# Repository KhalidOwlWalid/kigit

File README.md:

<div align="center">

# kigit

### Visual diffs for KiCad PCBs and schematics, straight from git.

</div>

**kigit** utilizes the use of git logs in order to allow user to perform diffs between their pcb and schematic files. It provides a proper visual feedback which helps in identifying changes made per commit basis. Hence where its name came from, combination of Ki from KiCAD and git itself (kigit!). 

What it can do:

- Compare your PCB between any two commits, visually
- Show what changed on your symbols and their fields
- Show your buses and where they're routed
- Works without git too: just point it at two folders
- Keep notes and PR-style discussions on why the board changed, and see any commit in 3D
- A bill of materials: part numbers, stock and prices from Mouser and Digi-Key, carts, your inventory, and builds you assemble board by board
- Comes with an example project to try it all on: `kigit example`

Have a look at the demos below to get a feel for it.

## Demonstration

Full documentation can be found here: https://khalidowlwalid.github.io/kigit/

### PCB diff
Hover a trace to light up its whole net and see what was added, removed or changed.

### Schematic diff
Every sheet, with nets computed the way KiCad's netlist does: hover a net, part or bus to see what changed.

### 3D Viewer
Kigit uses kicad-cli backend to render the PCB and displays the 2 commit's board side by side for ease of comparison

<p align="center"><i>The GUI: pick two commits, see what changed on the schematic and PCB, with both boards in 3D (made by KiCad) docked below, views linked.</i></p>

<p align="center"><i>Both commits' boards in 3D, side by side, with their views linked.</i></p>

### 3D diff (beta)
The comparison's changes on the board in 3D, in a tab of its own: parts added, changed, moved and removed, and the tracks that changed.

### Reviews and discussions
Review a commit with notes pinned to the parts and nets they're about, and ask for attention with PR-style discussions, all kept as Markdown in your project.

### Activity
A heatmap of your work on the board, day by day: comparisons, reviews, discussions and notes.

### Bill of materials
The BOM with the board in 2D and 3D beside it: hover a line to light up its parts. Fill in part numbers, look up stock and prices at Mouser and Digi-Key, export carts, track your inventory, and assemble builds board by board.

#### Looking up parts
Look up asks Mouser and Digi-Key about every line: stock, price for your boards, lead time and lifecycle, with progress you can follow by the bell. When a part is short or can't be found, kigit searches for others itself (by value and package, description or part family) for you to pick from.

#### Cart assistant
Import your Mouser or LCSC cart into a build: each line shows what's ordered, the board turns green where parts are covered and red where they're short, and rows kigit can't place get a suggested line to accept.

#### Assembly assistant
Assemble a build board by board: tick parts off as you place them (each comes out of your inventory), select several lines at once, and watch the board go from red (still to place) to green (placed).

---

## What kigit is not

kigit is an application that was built out of frustration of not having a kind of proper "git diff" for kicad for myself. Having came from a software background and being used to utilizing git versioning for all of my projects, not being able to do the same in a manner that I can compare my pcb and schematic visually between different commits without having to diff the .kicad_pcb and .kicad_sch files really frustates me. I am aware of the fact that there are other resources out there as shown below:

- [KiRI](https://github.com/leoheck/kiri)
- [KiCAD-Prism](https://krishna-swaroop.github.io/KiCAD-Prism/get-started/what-is-prism/)
- [KiHub](https://kihub.dev/)

They all have their pros and cons. KiRI is what got me excited about diffing schematics in the first place, and honestly, huge respect to the folks behind it. It's a great community effort, built well before AI was a thing.

The other two I didn't even know existed when I started. Funnily enough, not even Claude mentioned them when I first went looking for alternatives.

KiCAD-Prism and KiHub are in the same space and cover a lot of what kigit does. KiCAD-Prism is a whole package: free, open source, and the demos look amazing. But it needs a fair bit of Docker setup, which can be a turn-off if you're a hobbyist who just wants to design boards. KiHub needs a login, doesn't run offline, and is really aimed at teams collaborating (PR reviews and that kind of thing).

Me? I'm a hobbyist who only recently got into PCB design and out of this frustration, I figured: why not just make my own PCB diff that does just enough for what I need? Nothing fancy. It runs locally, it's a simple download, and it works on Linux and Windows. (Sorry macOS folks, I'm broke and not about to buy a Mac just for this.)

So, what kigit is **not** is a collaboration tool. It's for people who wants a simple app they can download, or open in a browser, to check what changed in their PCB designs. That's it.

## License

kigit is free and open source under the [MIT License](LICENSE): use it, fork it and change it, in public or private projects, with no need to open-source your own work. Third-party licenses are in [THIRD_PARTY_NOTICES.md](THIRD_PARTY_NOTICES.md).

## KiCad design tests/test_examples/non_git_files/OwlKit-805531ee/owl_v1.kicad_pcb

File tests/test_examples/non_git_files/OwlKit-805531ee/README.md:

# Owl Kit Board

STM32F103 development board for my personal use case to learn more about how microcontroller works.

## Specifications
- Programming interface: USB 2.0 Full Speed (12Mbit/s)
- CAN
- MicroSD card

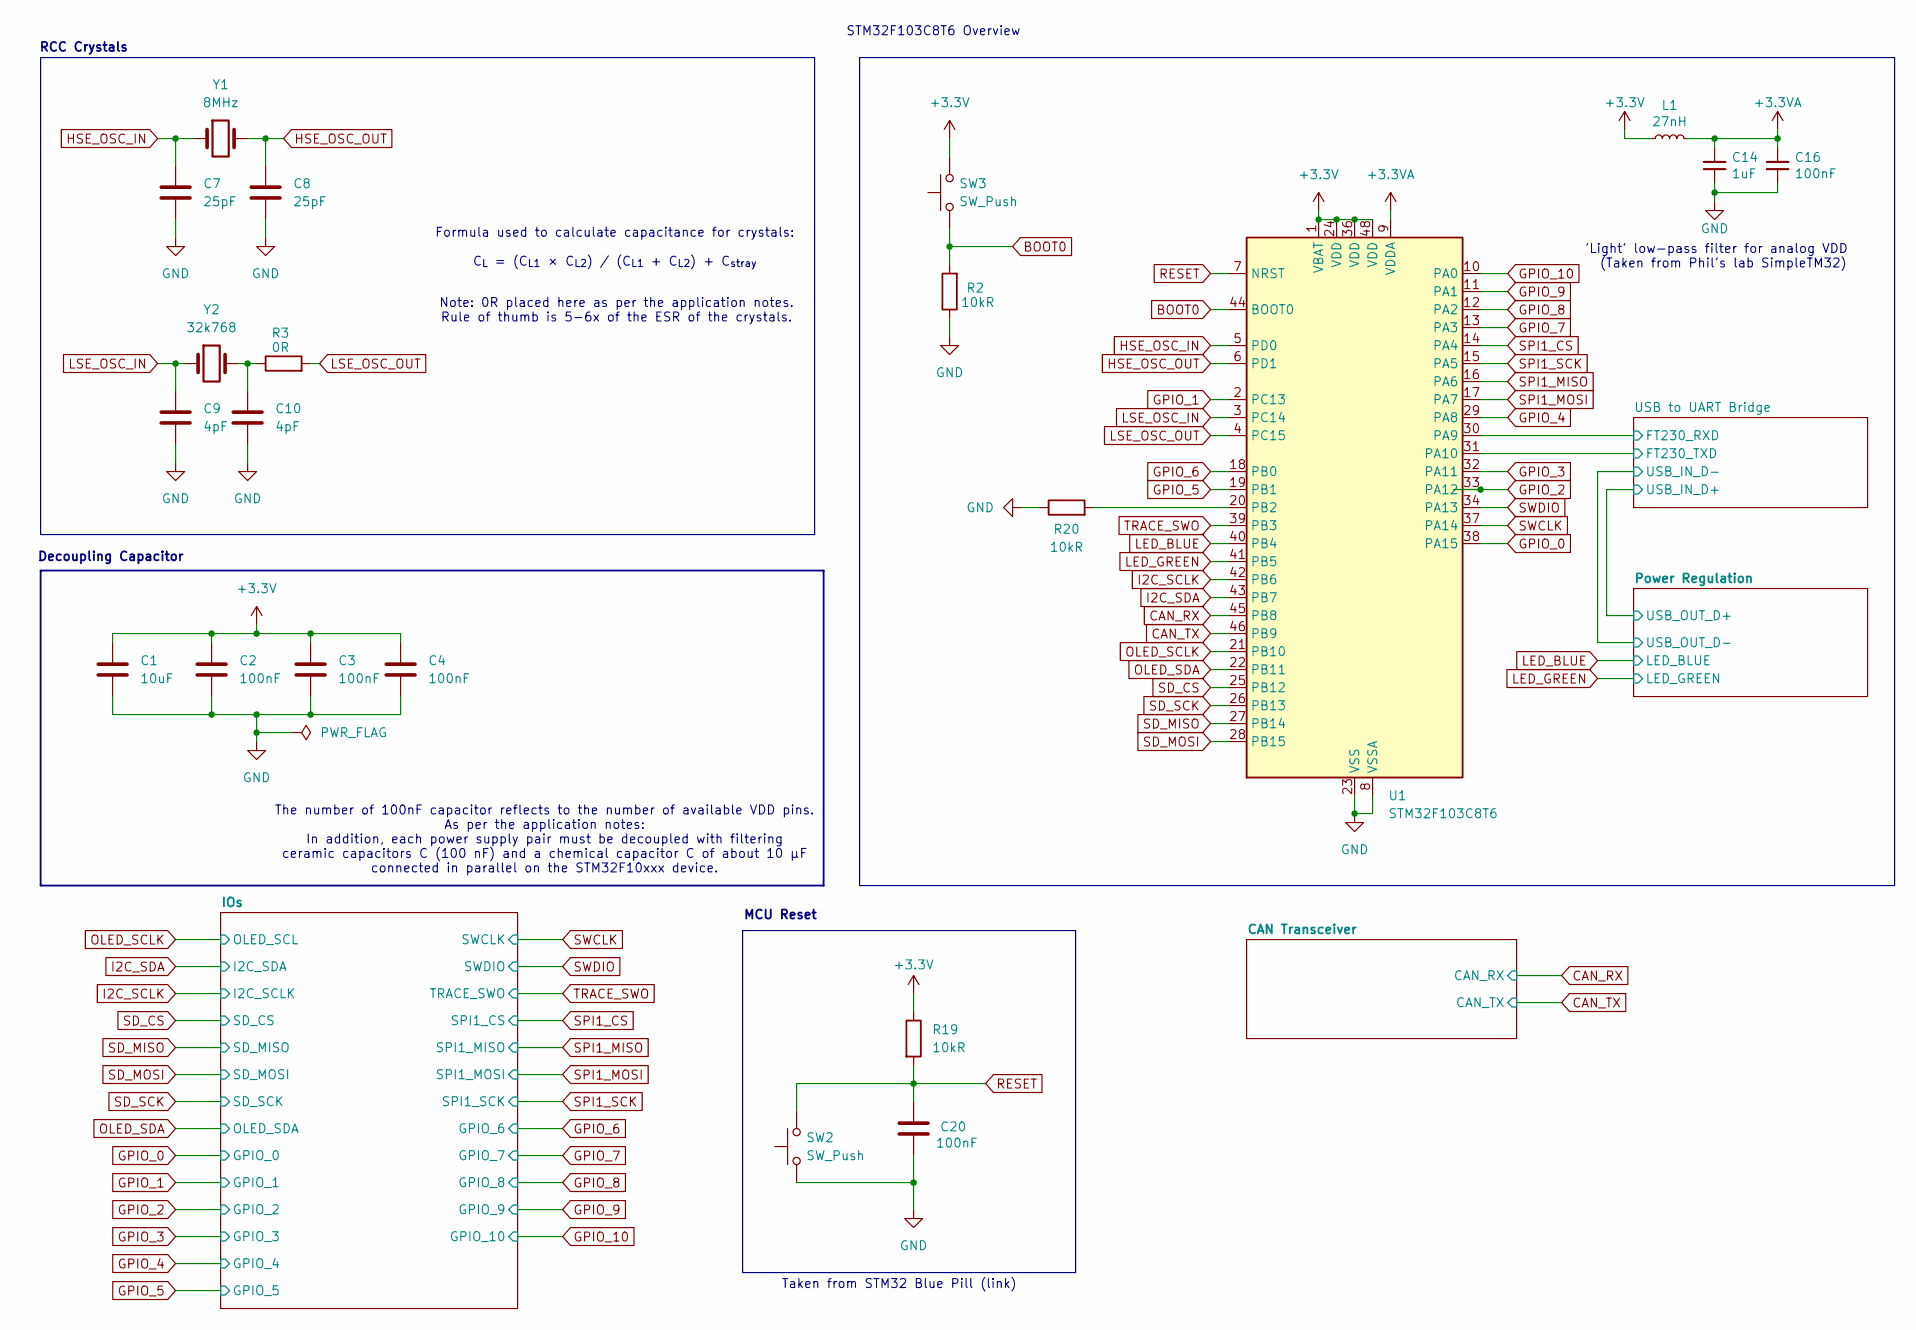
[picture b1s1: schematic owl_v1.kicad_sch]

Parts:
C1: 10uF; C_0603_1608Metric; MPN KGM15CT71A106MT
C2, C3, C4, C16, C20: 100nF; C_0603_1608Metric; MPN 0603ZC104K4T2A
C7, C8: 25pF; C_0603_1608Metric; MPN CSA0603C0G250J500JT; LCSC Part # C20069424
C9, C10: 4pF; C_0603_1608Metric; MPN 0603N5R0C100CT
C14: 1uF; C_0603_1608Metric; MPN CC0603KRX5R6BB105
L1: 27nH; L_0603_1608Metric; MPN AC0603FR-0727RL; Mouser 815-AISC0603R027GT
R2, R19, R20: 10kR; R_0603_1608Metric; MPN RC0603FR-0710KL; LCSC Part # C98220
R3: 0R; R_0603_1608Metric; MPN YAGEO; LCSC Part # C95177
SW2, SW3: SW_Push; SW_PUSH_6mm; MPN GR-YM-093
U1: STM32F103C8T6; LQFP-48_7x7mm_P0.5mm; MPN STM32F103C8T6
Y1: 8MHz; Crystal_SMD_HC49-SD; MPN ABLS3-8.000MHZ-D4Y-T
Y2: 32k768; Crystal_SMD_MicroCrystal_CC8V-T1A-2Pin_2.0x1.2mm_HandSolder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; MPN LFXTAL084885

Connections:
+3.3V: C1.1, C2.1, C3.1, C4.1, L1.1, R19.1, SW3.2, U1.1 (VBAT), U1.24 (VDD), U1.36 (VDD), U1.48 (VDD); also elsewhere on the board
+3.3VA: C14.1, C16.1, L1.2, U1.9 (VDDA)
/owl_v1/USB to UART Bridge/FT230_RXD: U1.30 (PA9); also elsewhere on the board
/owl_v1/USB to UART Bridge/FT230_TXD: U1.31 (PA10); also elsewhere on the board
BOOT0: R2.2, SW3.1, U1.44 (BOOT0)
CAN_RX: U1.45 (PB8); also elsewhere on the board
CAN_TX: U1.46 (PB9); also elsewhere on the board
GND: C1.2, C2.2, C3.2, C4.2, C7.2, C8.2, C9.2, C10.2, C14.2, C16.2, C20.1, R2.1, R20.1, SW2.1, U1.8 (VSSA), U1.23 (VSS), U1.35 (VSS), U1.47 (VSS); also elsewhere on the board
GPIO_0: U1.38 (PA15); also elsewhere on the board
GPIO_1: U1.2 (PC13); also elsewhere on the board
GPIO_2: U1.33 (PA12); also elsewhere on the board
GPIO_3: U1.32 (PA11); also elsewhere on the board
GPIO_4: U1.29 (PA8); also elsewhere on the board
GPIO_5: U1.19 (PB1); also elsewhere on the board
GPIO_6: U1.18 (PB0); also elsewhere on the board
GPIO_7: U1.13 (PA3); also elsewhere on the board
GPIO_8: U1.12 (PA2); also elsewhere on the board
GPIO_9: U1.11 (PA1); also elsewhere on the board
GPIO_10: U1.10 (PA0); also elsewhere on the board
HSE_OSC_IN: C7.1, U1.5 (PD0), Y1.1
HSE_OSC_OUT: C8.1, U1.6 (PD1), Y1.2
I2C_SCLK: U1.42 (PB6); also elsewhere on the board
I2C_SDA: U1.43 (PB7); also elsewhere on the board
LED_BLUE: U1.40 (PB4); also elsewhere on the board
LED_GREEN: U1.41 (PB5); also elsewhere on the board
LSE_OSC_IN: C9.1, U1.3 (PC14), Y2.1
LSE_OSC_OUT: R3.2, U1.4 (PC15)
unnamed: C10.1, R3.1, Y2.2
unnamed: R20.2, U1.20 (PB2)
OLED_SCLK: U1.21 (PB10); also elsewhere on the board
OLED_SDA: U1.22 (PB11); also elsewhere on the board
RESET: C20.2, R19.2, SW2.2, U1.7 (NRST)
SD_CS: U1.25 (PB12); also elsewhere on the board
SD_MISO: U1.27 (PB14); also elsewhere on the board
SD_MOSI: U1.28 (PB15); also elsewhere on the board
SD_SCK: U1.26 (PB13); also elsewhere on the board
SPI1_CS: U1.14 (PA4); also elsewhere on the board
SPI1_MISO: U1.16 (PA6); also elsewhere on the board
SPI1_MOSI: U1.17 (PA7); also elsewhere on the board
SPI1_SCK: U1.15 (PA5); also elsewhere on the board
SWCLK: U1.37 (PA14); also elsewhere on the board
SWDIO: U1.34 (PA13); also elsewhere on the board
TRACE_SWO: U1.39 (PB3); also elsewhere on the board

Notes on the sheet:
MCU Reset
Formula used to calculate capacitance for crystals: C_{L} = (C_{L1} × C_{L2}) / (C_{L1} + C_{L2}) + C_{stray}
RCC Crystals
STM32F103C8T6 Overview
The number of 100nF capacitor reflects to the number of available VDD pins. As per the application notes: In addition, each power supply pair must be decoupled with filtering ceramic capacitors C (100 nF) and a chemical capacitor C of about 10 μF connected in parallel on the STM32F10xxx device.
Decoupling Capacitor
Taken from STM32 Blue Pill (link)
Note: 0R placed here as per the application notes. Rule of thumb is 5-6x of the ESR of the crystals.
'Light' low-pass filter for analog VDD (Taken from Phil's lab SimpleTM32)

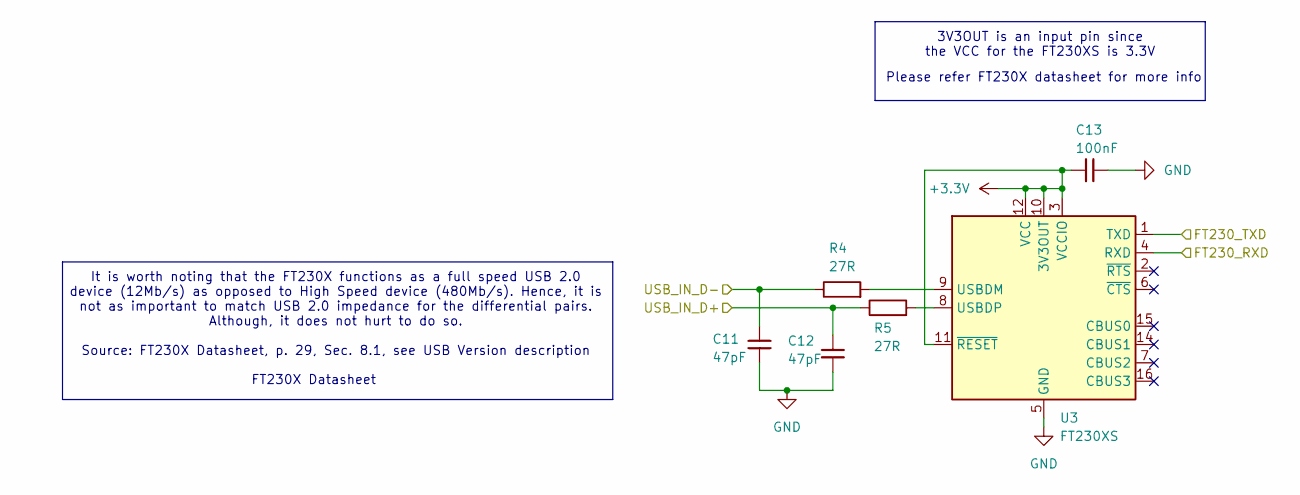
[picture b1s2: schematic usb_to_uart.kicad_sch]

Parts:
C11, C12: 47pF; C_0603_1608Metric; MPN 0603N470J100CT
C13: 100nF; C_0603_1608Metric; MPN 0603ZC104K4T2A
R4, R5: 27R; R_0603_1608Metric; MPN AC0603FR-0727RL
U3: FT230XS; SSOP-16_3.9x4.9mm_P0.635mm; MPN FT230XS-R; LCSC Part # C69082

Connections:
+3.3V: C13.2, U3.3 (VCCIO), U3.10 (3V3OUT), U3.11 (~RESET), U3.12 (VCC); also elsewhere on the board
/owl_v1/Power Regulation/USB_OUT_D+: C12.1, R5.1; also elsewhere on the board
/owl_v1/Power Regulation/USB_OUT_D-: C11.1, R4.1; also elsewhere on the board
/owl_v1/USB to UART Bridge/FT230_RXD: U3.4 (RXD); also elsewhere on the board
/owl_v1/USB to UART Bridge/FT230_TXD: U3.1 (TXD); also elsewhere on the board
GND: C11.2, C12.2, C13.1, U3.5 (GND), U3.13 (GND); also elsewhere on the board
unnamed: R4.2, U3.9 (USBDM)
unnamed: R5.2, U3.8 (USBDP)

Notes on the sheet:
Please refer FT230X datasheet for more info
3V3OUT is an input pin since the VCC for the FT230XS is 3.3V
FT230X Datasheet
It is worth noting that the FT230X functions as a full speed USB 2.0 device (12Mb/s) as opposed to High Speed device (480Mb/s). Hence, it is not as important to match USB 2.0 impedance for the differential pairs. Although, it does not hurt to do so. Source: FT230X Datasheet, p. 29, Sec. 8.1, see US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

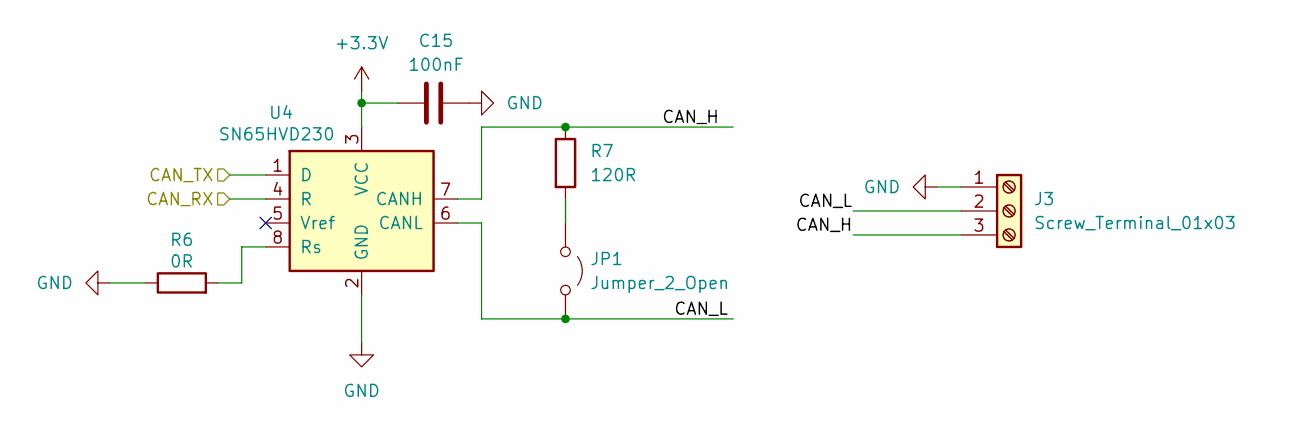
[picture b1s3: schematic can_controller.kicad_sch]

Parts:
C15: 100nF; C_0603_1608Metric; MPN 0603ZC104K4T2A
J3: Screw_Terminal_01x03; TerminalBlock_Phoenix_PT-1,5-3-3.5-H_1x03_P3.50mm_Horizontal; MPN ZB350
JP1: Jumper_2_Open; PinHeader_1x02_P2.54mm_Vertical; MPN G18450
R6: 0R; R_0603_1608Metric; MPN YAGEO; LCSC Part # C95177
R7: 120R; R_0603_1608Metric; MPN FRC0603F1200TS; LCSC Part # C2906988
U4: SN65HVD230; SOIC-8_3.9x4.9mm_P1.27mm; Voltage Rating 3.3; MPN SN65HVD230QDG4

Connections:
+3.3V: C15.1, U4.3 (VCC); also elsewhere on the board
/owl_v1/CAN Transceiver/CAN_H: J3.3, R7.1, U4.7 (CANH)
/owl_v1/CAN Transceiver/CAN_L: J3.2, JP1.2 (B), U4.6 (CANL)
CAN_RX: U4.4 (R); also elsewhere on the board
CAN_TX: U4.1 (D); also elsewhere on the board
GND: C15.2, J3.1, R6.1, U4.2 (GND); also elsewhere on the board
unnamed: JP1.1 (A), R7.2
unnamed: R6.2, U4.8 (Rs)

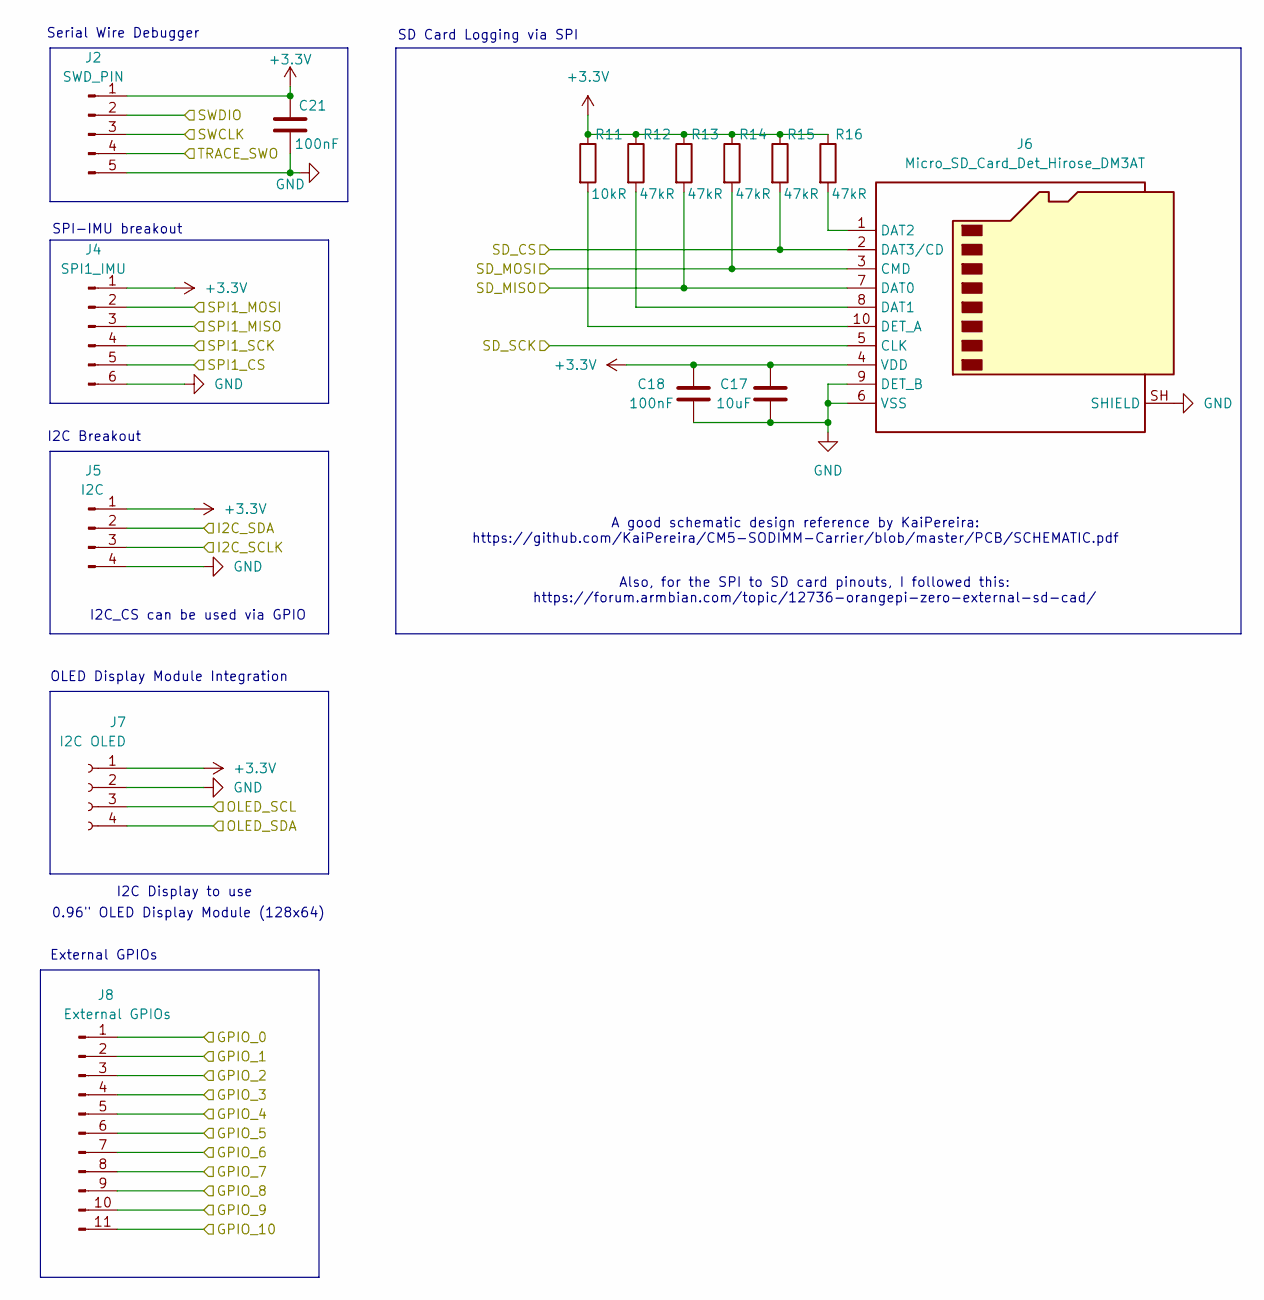
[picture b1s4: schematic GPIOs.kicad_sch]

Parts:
C17: 10uF; C_0603_1608Metric; MPN KGM15CT71A106MT
C18, C21: 100nF; C_0603_1608Metric; MPN 0603ZC104K4T2A
J2: SWD_PIN; PinHeader_1x05_P2.54mm_Vertical; MPN G18450
J4: SPI1_IMU; PinHeader_1x06_P2.54mm_Vertical; MPN G18450
J5: I2C; PinHeader_1x04_P2.54mm_Vertical; MPN G18450
J6: Micro_SD_Card_Det_Hirose_DM3AT; microSD_HC_Hirose_DM3AT-SF-PEJM5; MPN DM3AT-SF-PEJM5(40)
J7: I2C OLED; PinSocket_1x04_P2.54mm_Vertical; MPN G18450
J8: External GPIOs; PinHeader_1x11_P2.54mm_Vertical; MPN G18450
R11: 10kR; R_0603_1608Metric; MPN RC0603FR-0710KL; LCSC Part # C98220
R12, R13, R14, R15, R16: 47kR; R_0603_1608Metric; MPN FRC0603F4702TS; LCSC Part # C2907042

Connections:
+3.3V: C17.1, C18.1, C21.1, J2.1, J4.1, J5.1, J6.4 (VDD), J7.1, R11.1, R12.1, R13.1, R14.1, R15.1, R16.1; also elsewhere on the board
GND: C17.2, C18.2, C21.2, J2.5, J4.6, J5.4, J6.6 (VSS), J6.9 (DET_B), J6.SH (SHIELD), J7.2; also elsewhere on the board
GPIO_0: J8.1; also elsewhere on the board
GPIO_1: J8.2; also elsewhere on the board
GPIO_2: J8.3; also elsewhere on the board
GPIO_3: J8.4; also elsewhere on the board
GPIO_4: J8.5; also elsewhere on the board
GPIO_5: J8.6; also elsewhere on the board
GPIO_6: J8.7; also elsewhere on the board
GPIO_7: J8.8; also elsewhere on the board
GPIO_8: J8.9; also elsewhere on the board
GPIO_9: J8.10; also elsewhere on the board
GPIO_10: J8.11; also elsewhere on the board
I2C_SCLK: J5.3; also elsewhere on the board
I2C_SDA: J5.2; also elsewhere on the board
unnamed: J6.8 (DAT1), R12.2
unnamed: J6.1 (DAT2), R16.2
unnamed: J6.10 (DET_A), R11.2
OLED_SCLK: J7.3; also elsewhere on the board
OLED_SDA: J7.4; also elsewhere on the board
SD_CS: J6.2 (DAT3/CD), R15.2; also elsewhere on the board
SD_MISO: J6.7 (DAT0), R13.2; also elsewhere on the board
SD_MOSI: J6.3 (CMD), R14.2; also elsewhere on the board
SD_SCK: J6.5 (CLK); also elsewhere on the board
SPI1_CS: J4.5; also elsewhere on the board
SPI1_MISO: J4.3; also elsewhere on the board
SPI1_MOSI: J4.2; also elsewhere on the board
SPI1_SCK: J4.4; also elsewhere on the board
SWCLK: J2.3; also elsewhere on the board
SWDIO: J2.2; also elsewhere on the board
TRACE_SWO: J2.4; also elsewhere on the board

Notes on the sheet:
Also, for the SPI to SD card pinouts, I followed this: https://forum.armbian.com/topic/12736-orangepi-zero-external-sd-cad/
Serial Wire Debugger
External GPIOs
SD Card Logging via SPI
0.96" OLED Display Module (128x64)
I2C Breakout
I2C_CS can be used via GPIO
SPI-IMU breakout
OLED Display Module Integration
I2C Display to use
A good schematic design reference by KaiPereira: https://github.com/KaiPereira/CM5-SODIMM-Carrier/blob/master/PCB/SCHEMATIC.pdf

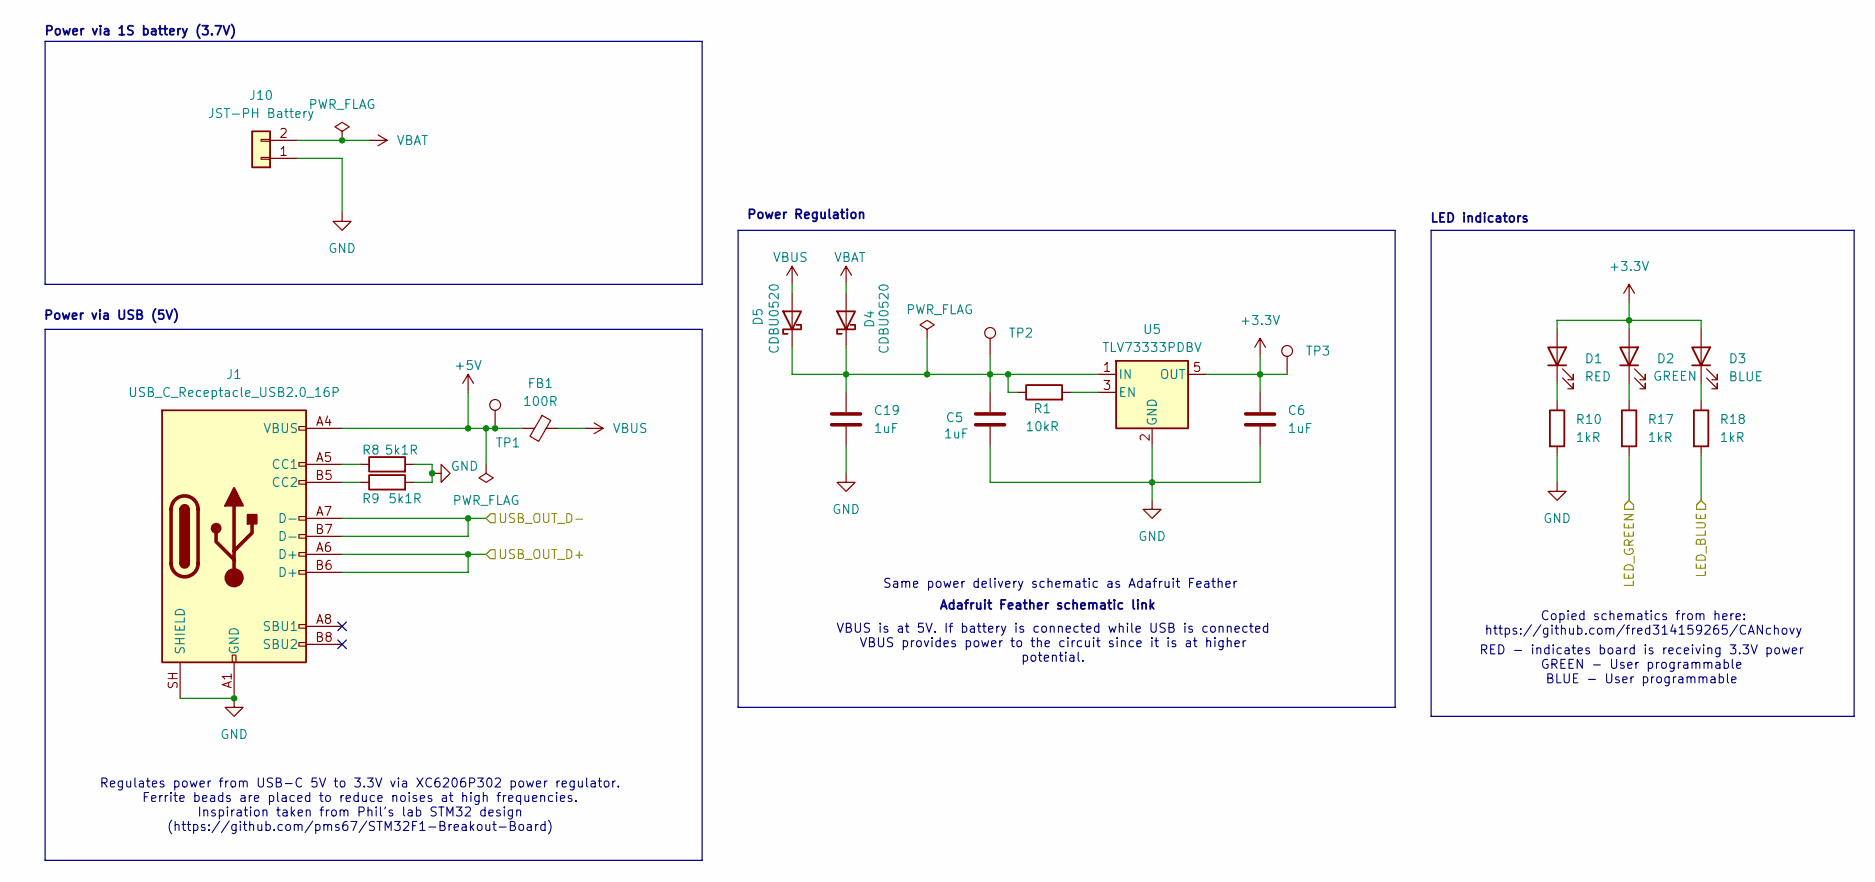
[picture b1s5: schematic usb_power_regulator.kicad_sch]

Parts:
C5, C6, C19: 1uF; C_0603_1608Metric; MPN CC0603KRX5R6BB105
D1: RED; LED_0603_1608Metric; MPN LTST-C191KEKT
D2: GREEN; LED_0603_1608Metric; MPN 150060GS84000
D3: BLUE; LED_0603_1608Metric; MPN 155060BS75300
D4, D5: CDBU0520; D_0603_1608Metric; MPN CDBU0520
FB1: 100R; L_0603_1608Metric; MPN ILHB0603ER101VHC42
J1: USB_C_Receptacle_USB2.0_16P; USB_C_Receptacle_GCT_USB4105-xx-A_16P_TopMnt_Horizontal; MPN UJ20-C-H-G-MSMT-4B-P16-TR
J10: JST-PH Battery; JST_PH_S2B-PH-K_1x02_P2.00mm_Horizontal; MPN S2B-PH-K-S-GW
R1: 10kR; R_0603_1608Metric; MPN RC0603FR-0710KL; LCSC Part # C98220
R8, R9: 5k1R; R_0603_1608Metric; MPN RC0603FR-075K1L; LCSC Part # C105580
R10, R17, R18: 1kR; R_0603_1608Metric; MPN RC0603FR-071KL; LCSC Part # C22548
TP1, TP2, TP3: TestPoint_Pad_D1.5mm; MPN None
U5: TLV73333PDBV; SOT-23-5; MPN TLV73333PDBVT; Mouser 595-REG113NA-33250G4

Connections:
+3.3V: C6.1, D1.2 (A), D2.2 (A), D3.2 (A), TP3.1 (1_1), U5.5 (OUT); also elsewhere on the board
+5V: FB1.2, J1.A4 (VBUS), J1.A9 (VBUS), J1.B4 (VBUS), J1.B9 (VBUS), TP1.1 (1_1)
/owl_v1/Power Regulation/USB_OUT_D+: J1.A6 (D+), J1.B6 (D+); also elsewhere on the board
/owl_v1/Power Regulation/USB_OUT_D-: J1.A7 (D-), J1.B7 (D-); also elsewhere on the board
GND: C5.2, C6.2, C19.2, J1.A1 (GND), J1.A12 (GND), J1.B1 (GND), J1.B12 (GND), J1.SH (SHIELD), J10.1, R8.2, R9.2, R10.2, U5.2 (GND); also elsewhere on the board
LED_BLUE: R18.2; also elsewhere on the board
LED_GREEN: R17.2; also elsewhere on the board
unnamed: D1.1 (K), R10.1
unnamed: D2.1 (K), R17.1
unnamed: D3.1 (K), R18.1
unnamed: C5.1, C19.1, D4.1 (K), D5.1 (K), R1.1, TP2.1 (1_1), U5.1 (IN)
unnamed: J1.A5 (CC1), R8.1
unnamed: J1.B5 (CC2), R9.1
unnamed: R1.2, U5.3 (EN)
VBAT: D4.2 (A), J10.2
VBUS: D5.2 (A), FB1.1

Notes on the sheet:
VBUS is at 5V. If battery is connected while USB is connected VBUS provides power to the circuit since it is at higher potential.
Same power delivery schematic as Adafruit Feather
LED indicators
RED - indicates board is receiving 3.3V power GREEN - User programmable BLUE - User programmable
Regulates power from USB-C 5V to 3.3V via XC6206P302 power regulator. Ferrite beads are placed to reduce noises at high frequencies. Inspiration taken from Phil's lab STM32 design (https://github.com/pms67/STM32F1-Breakout-Board)
Copied schematics from here: https://github.com/fred314159265/CANchovy
Power via USB (5V)
Power Regulation
Power via 1S battery (3.7V)
Adafruit Feather schematic link

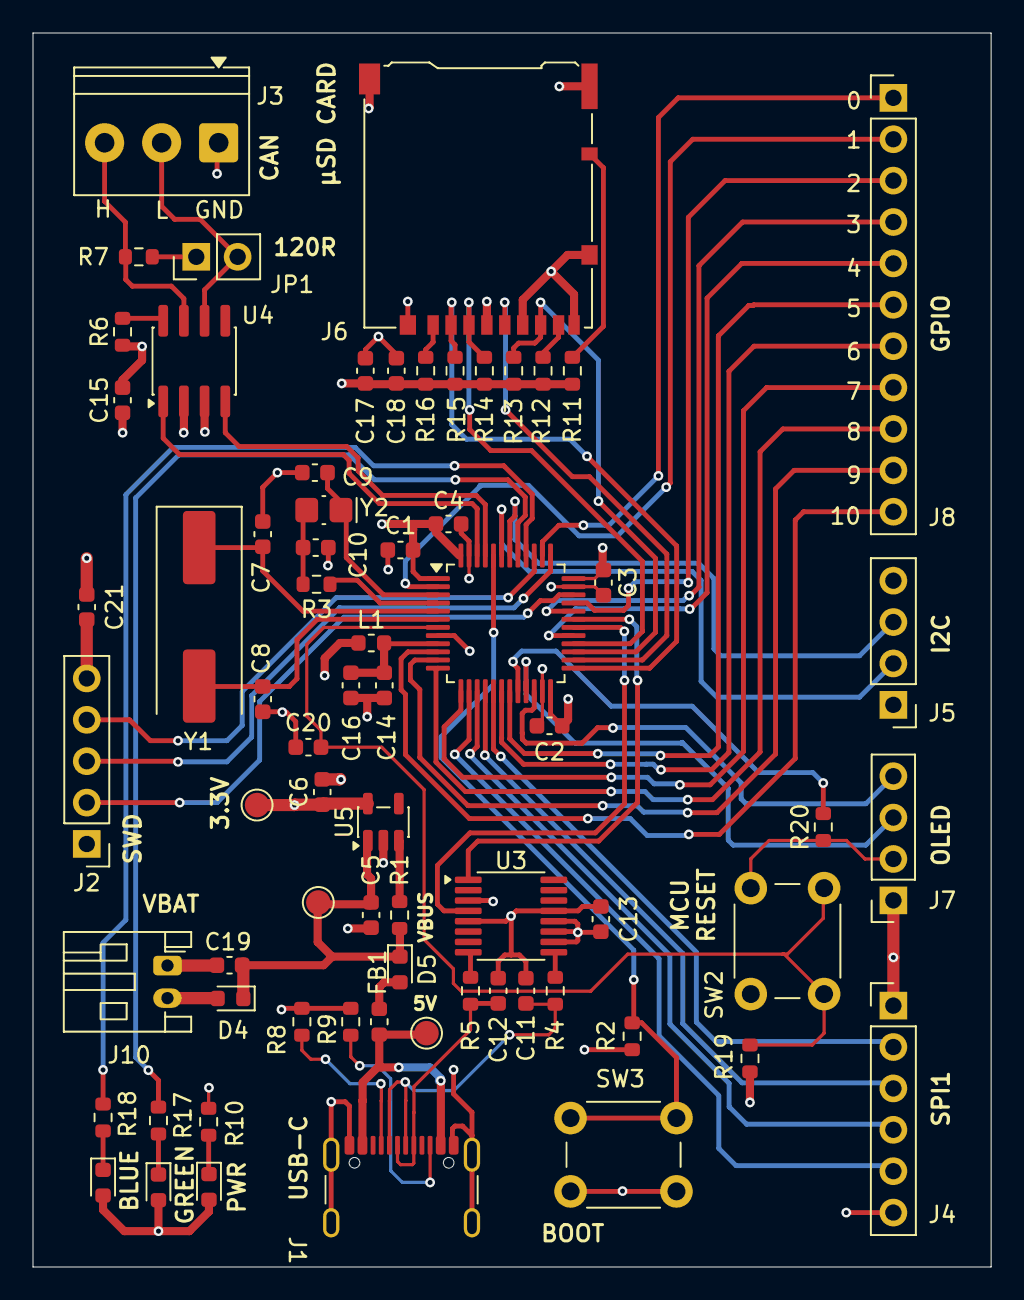
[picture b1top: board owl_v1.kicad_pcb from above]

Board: 4 copper layers, 58.8 x 75.7 mm, 70 parts (1 on the bottom side), 64 nets.

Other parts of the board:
Owl Kit v0.1: LOGO

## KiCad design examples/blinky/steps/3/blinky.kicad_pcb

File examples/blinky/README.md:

# blinky: the kigit example

Project snapshots, one per commit, that `kigit example` turns into a git repository to try kigit on. Made by `tools/make_example.py`; don't edit by hand.

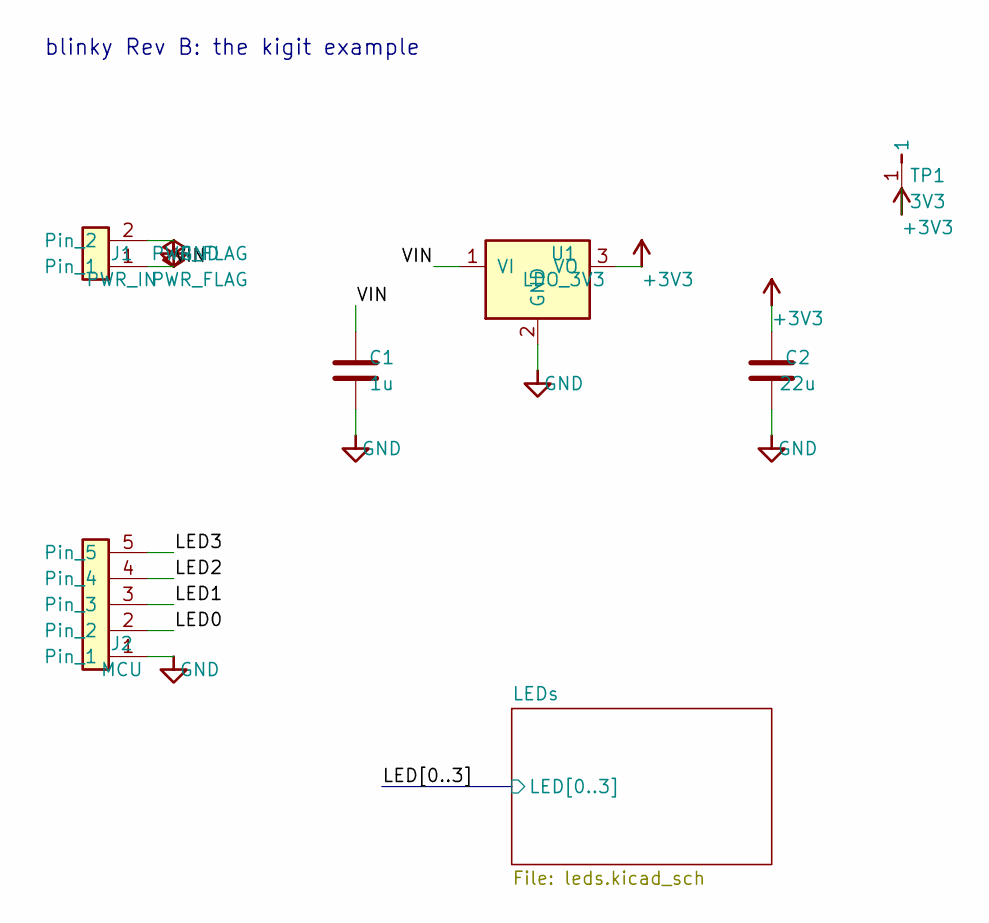
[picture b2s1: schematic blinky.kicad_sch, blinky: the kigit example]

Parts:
C1: 1u; C_0603_1608Metric
C2: 22u; C_0603_1608Metric
J1: PWR_IN; PinHeader_1x02_P2.54mm_Vertical
J2: MCU; PinHeader_1x05_P2.54mm_Vertical
TP1: 3V3; TestPoint_Pad_D1.0mm
U1: LDO_3V3; SOT-23

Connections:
+3V3: C2.1, TP1.1, U1.3 (VO); also elsewhere on the board
/LED0: J2.2; also elsewhere on the board
/LED1: J2.3; also elsewhere on the board
/LED2: J2.4; also elsewhere on the board
/LED3: J2.5; also elsewhere on the board
/VIN: C1.1, J1.1, U1.1 (VI)
GND: C1.2, C2.2, J1.2, J2.1, U1.2 (GND)

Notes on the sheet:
blinky Rev B: the kigit example

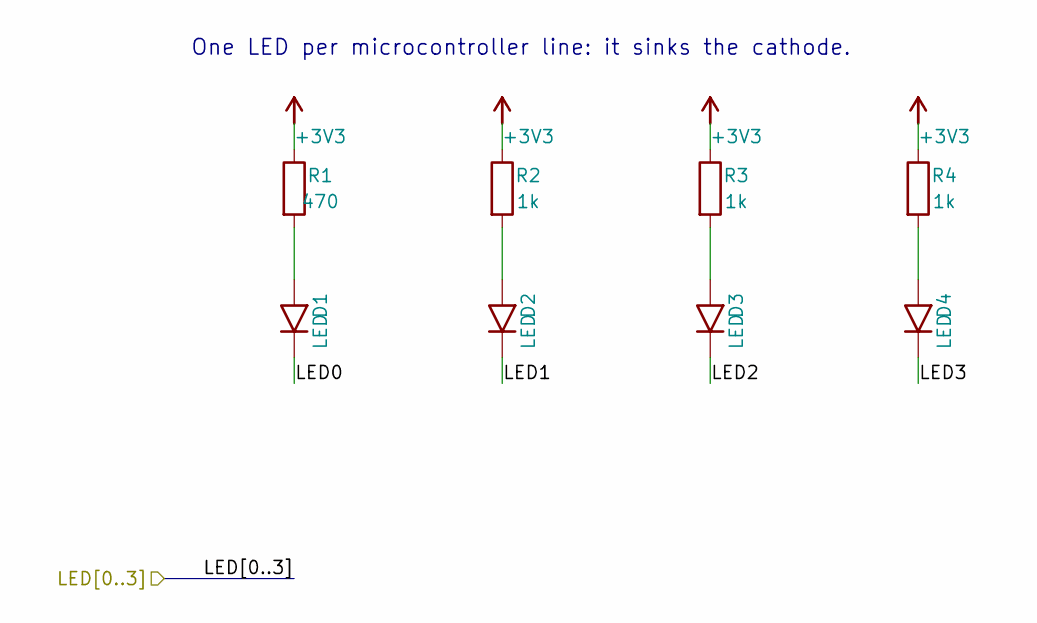
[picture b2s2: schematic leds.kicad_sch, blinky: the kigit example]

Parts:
D1, D2, D3, D4: LED; LED_0603_1608Metric
R1: 470; R_0603_1608Metric
R2, R3, R4: 1k; R_0603_1608Metric

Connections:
+3V3: R1.1, R2.1, R3.1, R4.1; also elsewhere on the board
/LED0: D1.1 (K); also elsewhere on the board
/LED1: D2.1 (K); also elsewhere on the board
/LED2: D3.1 (K); also elsewhere on the board
/LED3: D4.1 (K); also elsewhere on the board
unnamed: D1.2 (A), R1.2
unnamed: D2.2 (A), R2.2
unnamed: D3.2 (A), R3.2
unnamed: D4.2 (A), R4.2

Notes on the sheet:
One LED per microcontroller line: it sinks the cathode.

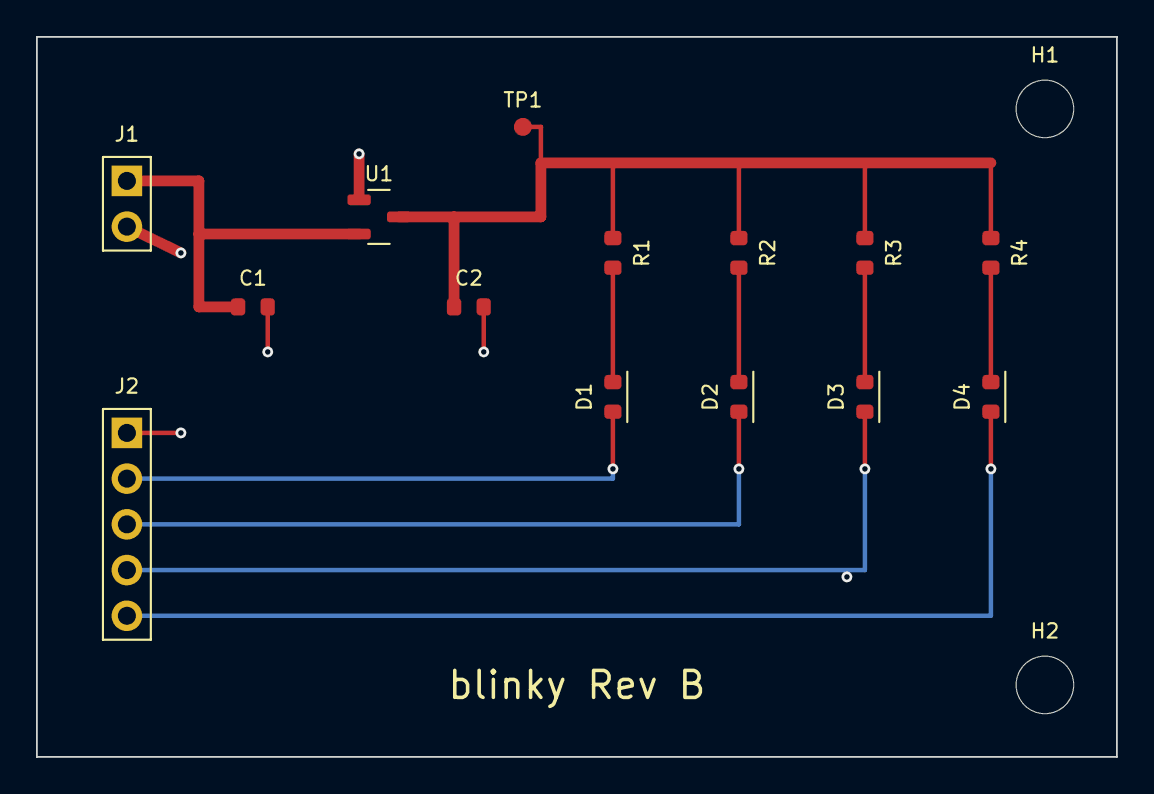
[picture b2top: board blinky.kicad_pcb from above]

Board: 2 copper layers, 60.0 x 40.0 mm, 16 parts (0 on the bottom side), 11 nets.

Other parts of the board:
H1, H2: MountingHole; MountingHole_3.2mm_M3

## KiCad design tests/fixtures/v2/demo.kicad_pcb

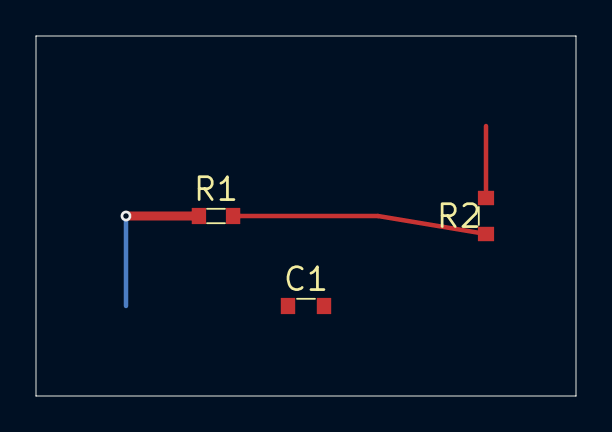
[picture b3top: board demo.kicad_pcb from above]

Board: 2 copper layers, 30.0 x 20.0 mm, 3 parts (0 on the bottom side), 3 nets.

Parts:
C1: 1k; R
R1, R2: 1k; R

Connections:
GND: C1.2, R2.2
SIG: R1.2, R2.1
VCC: C1.1, R1.1
